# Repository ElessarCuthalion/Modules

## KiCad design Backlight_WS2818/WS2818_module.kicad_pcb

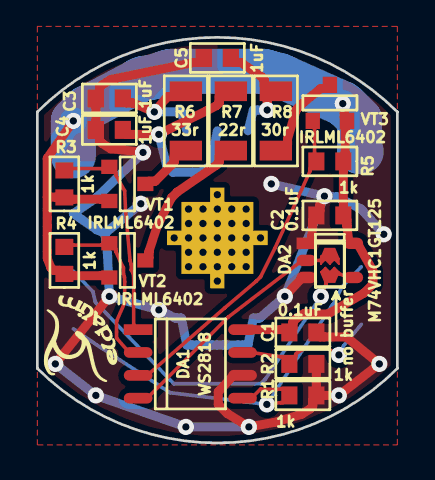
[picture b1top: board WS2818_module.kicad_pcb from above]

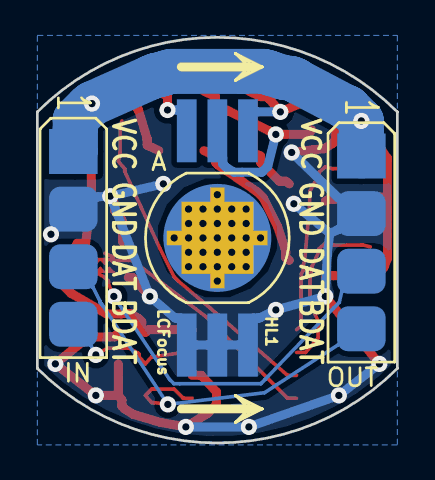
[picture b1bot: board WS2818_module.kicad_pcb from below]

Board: 2 copper layers, 20.0 x 22.5 mm, 23 parts (3 on the bottom side), 15 nets.

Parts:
C1, C2: 0.1uF; CAP0603
C3, C4, C5: 1uF; CAP0603
DA1: WS2818; SOP8
DA2: M74VHC1GT125; SOT23-5
HL1: LCFocus; LCFocus_6pin+PAD
Logo1: Eldalim; Eldalim_5x4
R1, R2, R3, R4, R5: 1k; RES0603
R6: 33r; RES1206
R7: 22r; RES1206
R8: 30r; RES1206
VT1, VT2, VT3: IRLML6402; SOT23-3
XP1: IN; for_WS2813_AVX_00-9176
XP2: OUT; for_WS2813_AVX_00-9176
fus1: no buffer; FuseSolder

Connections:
+VCC: C1.1, C2.1, DA1.8, DA2.5, R3.1, R4.1, R5.1, VT1.2, VT2.2, VT3.2, XP1.1, XP2.1
/BDin: DA1.7, R2.1, XP1.4
/B_pwm: DA1.3, R5.2, VT3.1
/Bin: R8.1, VT3.3
/Bout: C5.1, HL1.BA, R8.2
/Din: DA1.5, R1.1, XP1.3, XP2.4
/Dout: DA2.4, XP2.3, fus1.2
/G_pwm: DA1.2, R4.2, VT2.1
/Gin: R7.1, VT2.3
/Gout: C4.1, HL1.GA, R7.2
/R_pwm: DA1.1, R3.2, VT1.1
/Rin: R6.1, VT1.3
/Rout: C3.1, HL1.RA, R6.2
GND: C1.2, C2.2, C3.2, C4.2, C5.2, DA1.6, DA2.1, DA2.3, HL1.BC, HL1.GC, HL1.RC, R1.2, R2.2, XP1.2, XP2.2
unnamed: DA1.4, DA2.2, fus1.1

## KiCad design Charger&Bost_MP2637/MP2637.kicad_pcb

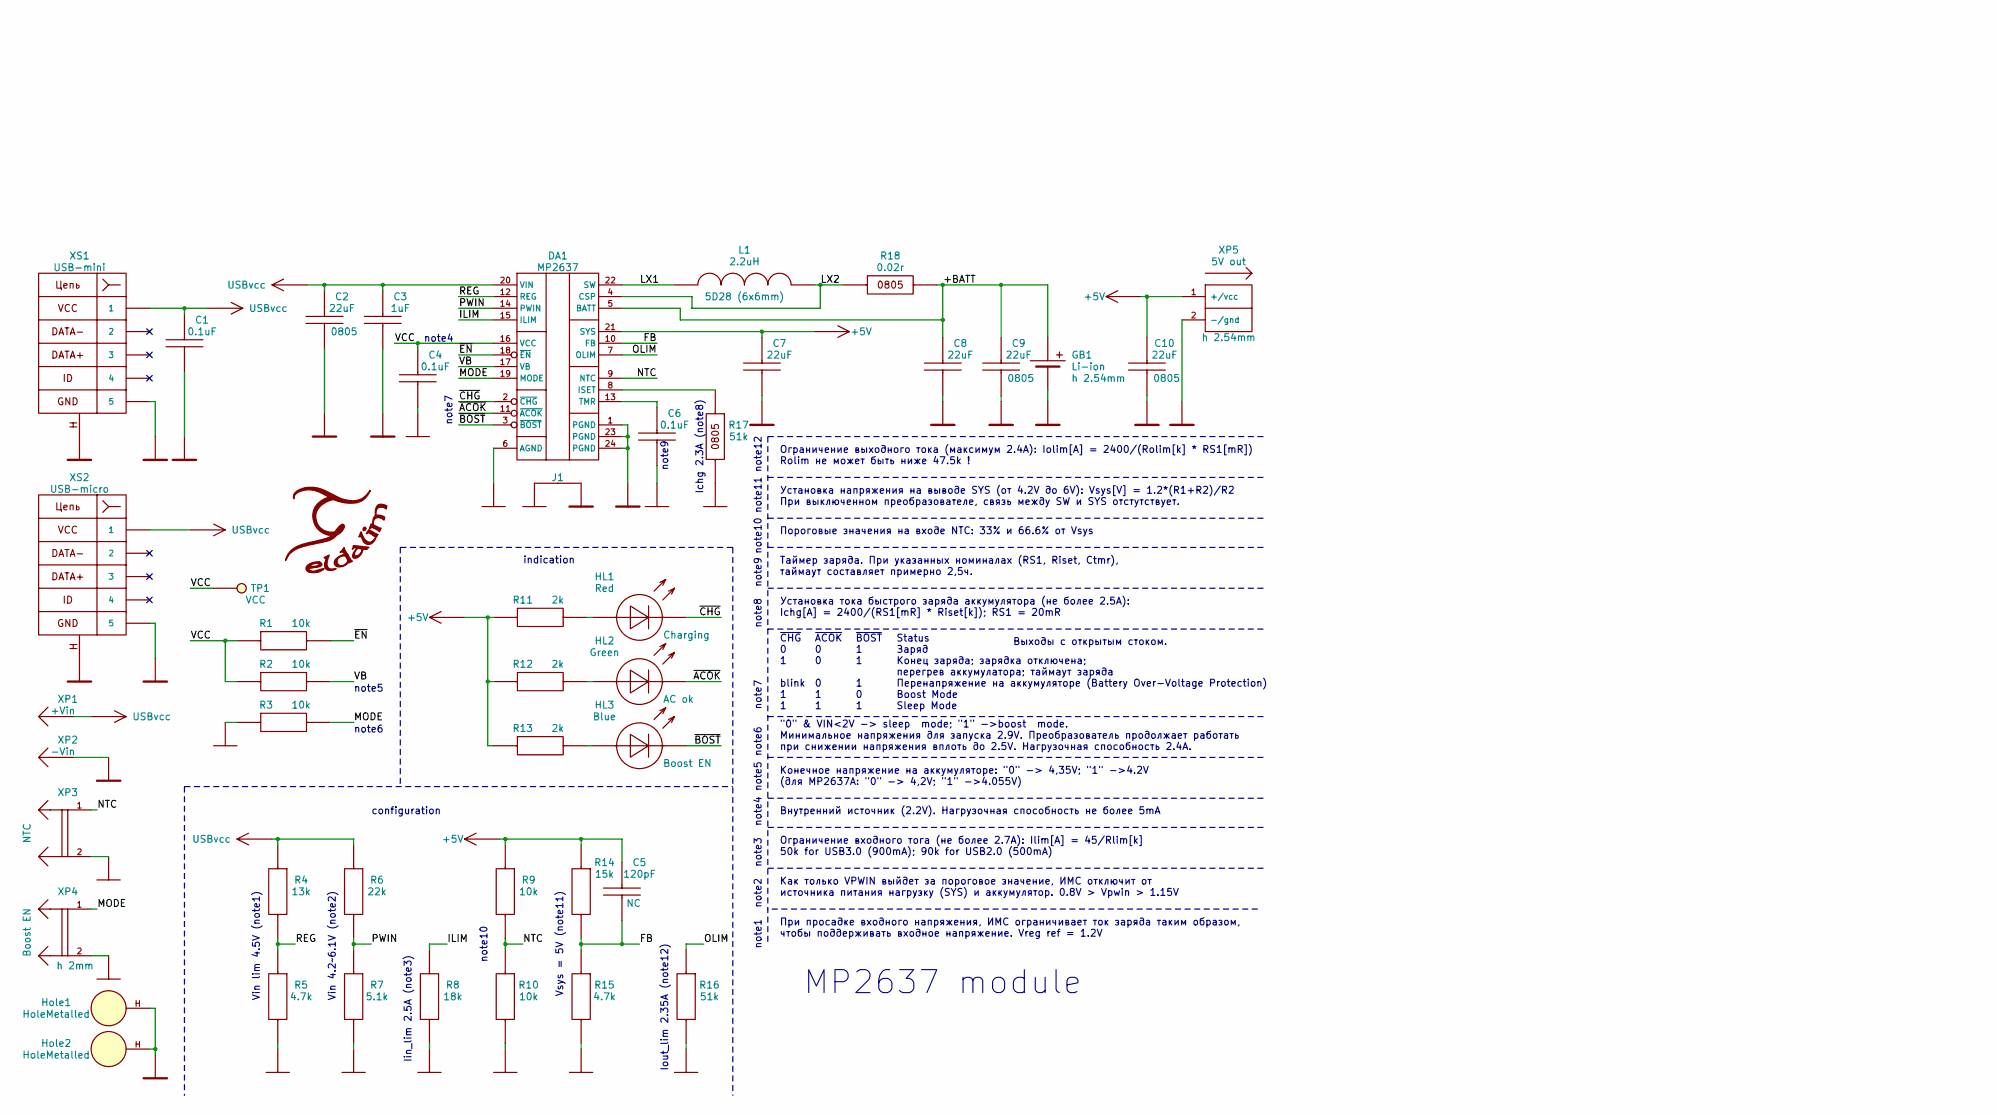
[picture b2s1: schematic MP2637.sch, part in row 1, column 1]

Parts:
C1, C4, C6: 0.1uF; CAP0603
C2, C9, C10: 22uF; CAP0805
C3: 1uF; CAP0603
C5: 120pF; CAP0603
C7, C8: 22uF; CAP0603
DA1: MP2637; FCQFN24
GB1: Li-ion; for_PolarOut_PLS-2
HL1: Red; LED0805
HL2: Green; LED0805
HL3: Blue; LED0805
Hole1, Hole2: HoleMetalled; Hole_for_M3_small
J1: Jumper
L1: 2.2uH; IND_6x6_5D28
Label1: Eldalim; Eldalim_17x15_back
R1, R2, R3, R9, R10: 10k; RES0603
R4: 13k; RES0603
R5, R15: 4.7k; RES0603
R6: 22k; RES0603
R7: 5.1k; RES0603
R8: 18k; RES0603
R11, R12, R13: 2k; RES0603
R14: 15k; RES0603
R16: 51k; RES0603
R17: 51k; RES0805
R18: 0.02r; RES0805
TP1: VCC; TestPoint_1mm
XP1: +Vin; PLS-1
XP2: -Vin; PLS-1Rnd
XP3: NTC; PLS-2
XP4: Boost EN; PLS2-2
XP5: 5V out; for_PolarOut_PLS-2
XS1: USB-mini; USB-mini_B
XS2: USB-micro; USB-micro_B

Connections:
+5V: C5.1, C7.1, C10.1, DA1.21 (SYS), R9.1, R11.1, R12.1, R13.1, R14.1, XP5.1 (+/vcc)
+USBvcc: C1.1, C2.1, C3.1, DA1.20 (VIN), R4.1, R6.1, XP1.1, XS1.1, XS2.1
/+BATT: C8.1, C9.1, DA1.5 (BATT), GB1.1 (+), R18.2
/FB: C5.2, DA1.10 (FB), R14.2, R15.1
/ILIM: DA1.15 (ILIM), R8.1
/LX1: DA1.22 (SW), L1.1
/LX2: DA1.4 (CSP), L1.2, R18.1
/MODE: DA1.19 (MODE), R3.2, XP4.1
/NTC: DA1.9 (NTC), R9.2, R10.1, XP3.1
/OLIM: DA1.7 (OLIM), R16.1
/PWIN: DA1.14 (PWIN), R6.2, R7.1
/REG: DA1.12 (REG), R4.2, R5.1
/VB: DA1.17 (VB), R2.2
/VCC: C4.1, DA1.16 (VCC), R1.1, R2.1, TP1.1
/~ACOK: DA1.11 (~ACOK), HL2.C
/~BOST: DA1.3 (~BOST), HL3.C
/~CHG: DA1.2 (~CHG), HL1.C
/~EN: DA1.18 (~EN), R1.2
GND: C4.2, C6.2, DA1.6 (AGND), J1.1, R3.1, R5.2, R7.2, R8.2, R10.2, R15.2, R16.2, R17.2, XP3.2, XP4.2
GNDP: C1.2, C2.2, C3.2, C7.2, C8.2, C9.2, C10.2, DA1.1 (PGND), DA1.23 (PGND), DA1.24 (PGND), GB1.2 (-), Hole1.H, Hole2.H, J1.2, XP2.1, XP5.2 (-/gnd), XS1.5, XS1.SHLD, XS2.5, XS2.SHLD
unnamed: C6.1, DA1.13 (TMR)
unnamed: DA1.8 (ISET), R17.1
unnamed: HL1.A, R11.2
unnamed: HL2.A, R12.2
unnamed: HL3.A, R13.2

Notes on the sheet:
MP2637 module
Внутренний источник (2.2V). Нагрузочная способность не более 5mA
note2
note1
note4
При просадке входного напряжения, ИМС ограничивает ток заряда таким образом, чтобы поддерживать входное напряжение. Vreg ref = 1.2V
note3
"0" & VIN<2V -> sleep mode; "1" ->boost mode. Минимальное напряжения для запуска 2.9V. Преобразователь продолжает работать при снижении напряжения вплоть до 2.5V. Нагрузочная способность 2.4A.
note5
Конечное напряжение на аккумуляторе: "0" -> 4,35V; "1" ->4.2V (для MP2637A: "0" -> 4,2V; "1" ->4.055V)
note6
Vin lim 4.5V (note1)
Vin 4.2~~6.1V (note2)
Пороговые значения на входе NTC: 33% и 66.6% от Vsys
Как только VPWIN выйдет за пороговое значение, ИМС отключит от источника питания нагрузку (SYS) и аккумулятор. 0.8V > Vpwin > 1.15V
Iin_lim 2.5A (note3)
Ограничение входного тога (не более 2.7A): Ilim[A] = 45/Rlim[k] 50k for USB3.0 (900mA); 90k for USB2.0 (500mA)
note7
Выходы с открытым стоком.
Status Заряд Конец заряда; зарядка отключена; перегрев аккумулатора; таймаут заряда Перенапряжение на аккумуляторе (Battery Over-Voltage Protection) Boost Mode Sleep Mode
~CHG~ 0 1 blink 1 1
~ACOK~ 0 0 0 1 1
~BOST~ 1 1 1 0 1
indication
note9
Ichg 2.3A (note8)
note8
Установка тока быстрого заряда аккумулятора (не более 2.5A): Ichg[A] = 2400/(RS1[mR] * Riset[k]); RS1 = 20mR
Таймер заряда. При указанных номиналах (RS1, Riset, Ctmr), таймаут составляет примерно 2,5ч.
note10
Установка напряжения на выводе SYS (от 4.2V до 6V): Vsys[V] = 1.2*(R1+R2)/R2 При выключенном преобразователе, связь между SW и SYS отстутствует.
Vsys = 5V (note11)
configuration
note11
note12
Ограничение выходного тока (максимум 2.4A): Iolim[A] = 2400/(Rolim[k] * RS1[mR]) Rolim не может быть ниже 47.5k !
Iout_lim 2.35A (note12)

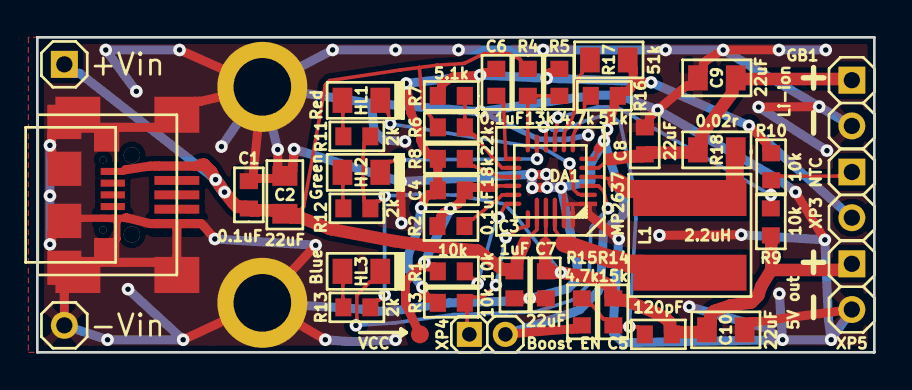
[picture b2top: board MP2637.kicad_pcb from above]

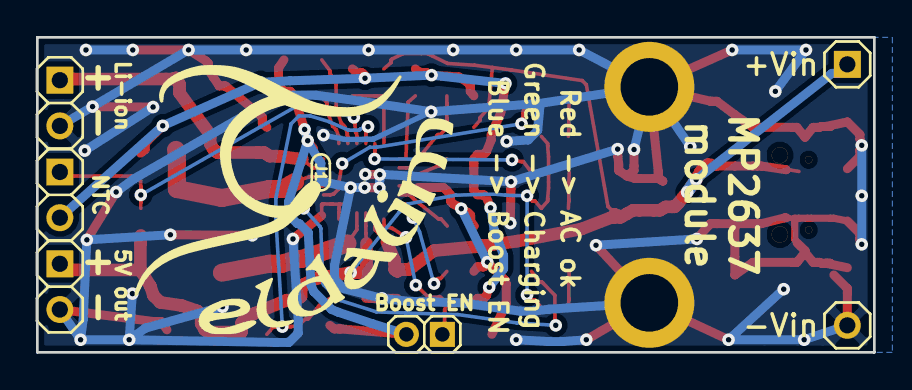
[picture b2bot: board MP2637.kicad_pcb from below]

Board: 2 copper layers, 46.5 x 17.5 mm, 46 parts (3 on the bottom side), 25 nets.

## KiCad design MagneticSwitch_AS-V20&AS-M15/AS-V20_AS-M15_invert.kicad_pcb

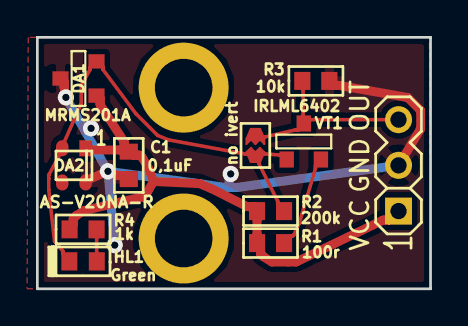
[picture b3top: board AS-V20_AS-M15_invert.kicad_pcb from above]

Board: 2 copper layers, 21.8 x 14.0 mm, 14 parts (1 on the bottom side), 6 nets.

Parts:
C1: 0,1uF; CAP0603
DA1: MRMS201A; SOT23-3
DA2: AS-V20NA-R; SON4
HL1: Green; LED0603
HOLE1, HOLE2: HOLE_METALLED; Hole_for_M3_small
Logo1: Eldalim; Eldalim_10x8_back
R1: 100r; RES0603
R2: 200k; RES0603
R3: 10k; RES0603
R4: 1k; RES0603
VT1: IRLML6402; SOT23-3
XP1: for_SENS; for_SENS_PLS-3
fuse1: no ivert; FuseSolder

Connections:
/SensIn: DA1.2, DA2.2, HL1.C, R2.2, VT1.1, fuse1.2
/SensOut: R3.1, VT1.3, XP1.3, fuse1.1
/VCC: C1.1, DA1.1, DA2.1, R1.1, R2.1, R4.1, XP1.1
GND: C1.2, DA1.3, DA2.4, R3.2, XP1.2
unnamed: HL1.A, R4.2
unnamed: R1.2, VT1.2

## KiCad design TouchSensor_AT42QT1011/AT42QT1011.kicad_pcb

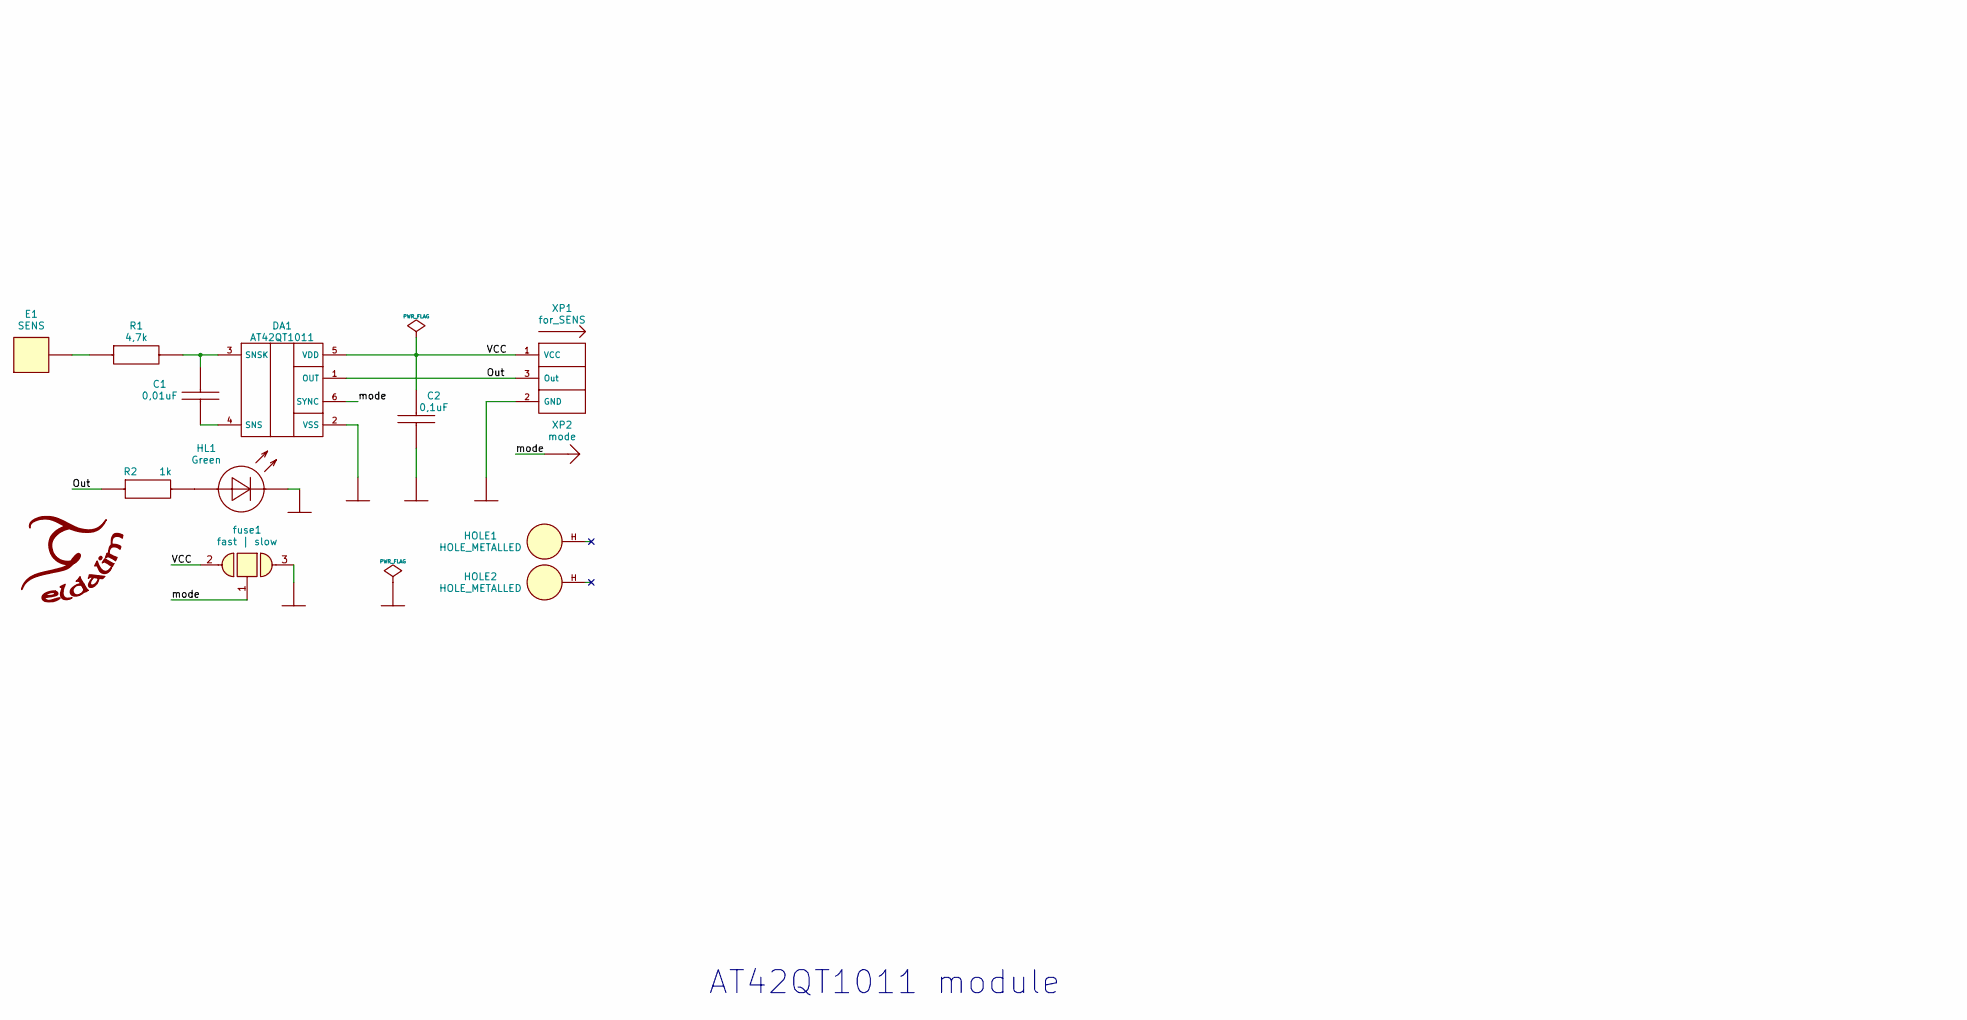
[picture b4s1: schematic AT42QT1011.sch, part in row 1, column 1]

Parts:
C1: 0,01uF; CAP0805
C2: 0,1uF; CAP0603
DA1: AT42QT1011; SOT23-6
E1: SENS; PBS-1
HL1: Green; LED0603
HOLE1, HOLE2: HOLE_METALLED; Hole_for_M3_small
Logo1: Eldalim; Eldalim_10x8_back
R1: 4,7k; RES0805
R2: 1k; RES0603
XP1: for_SENS; for_SENS_PLS-3
XP2: mode; PLS-1Rnd
fuse1: fast | slow; FuseSolder_x2_0603

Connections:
/Out: DA1.1 (OUT), R2.1, XP1.3 (Out)
/VCC: C2.1, DA1.5 (VDD), XP1.1 (VCC), fuse1.2
/mode: DA1.6 (SYNC), XP2.1, fuse1.1
GND: C2.2, DA1.2 (VSS), HL1.C, XP1.2 (GND), fuse1.3
unnamed: C1.1, DA1.3 (SNSK), R1.2
unnamed: C1.2, DA1.4 (SNS)
unnamed: E1.1, R1.1
unnamed: HL1.A, R2.2

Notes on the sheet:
AT42QT1011 module

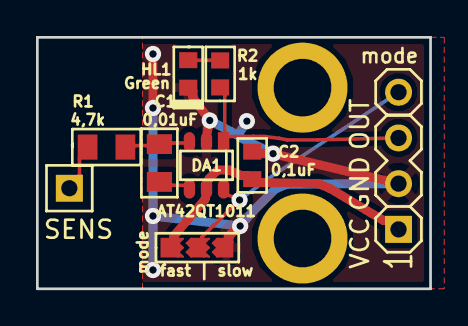
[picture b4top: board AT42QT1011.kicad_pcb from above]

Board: 2 copper layers, 21.8 x 14.0 mm, 13 parts (1 on the bottom side), 8 nets.
